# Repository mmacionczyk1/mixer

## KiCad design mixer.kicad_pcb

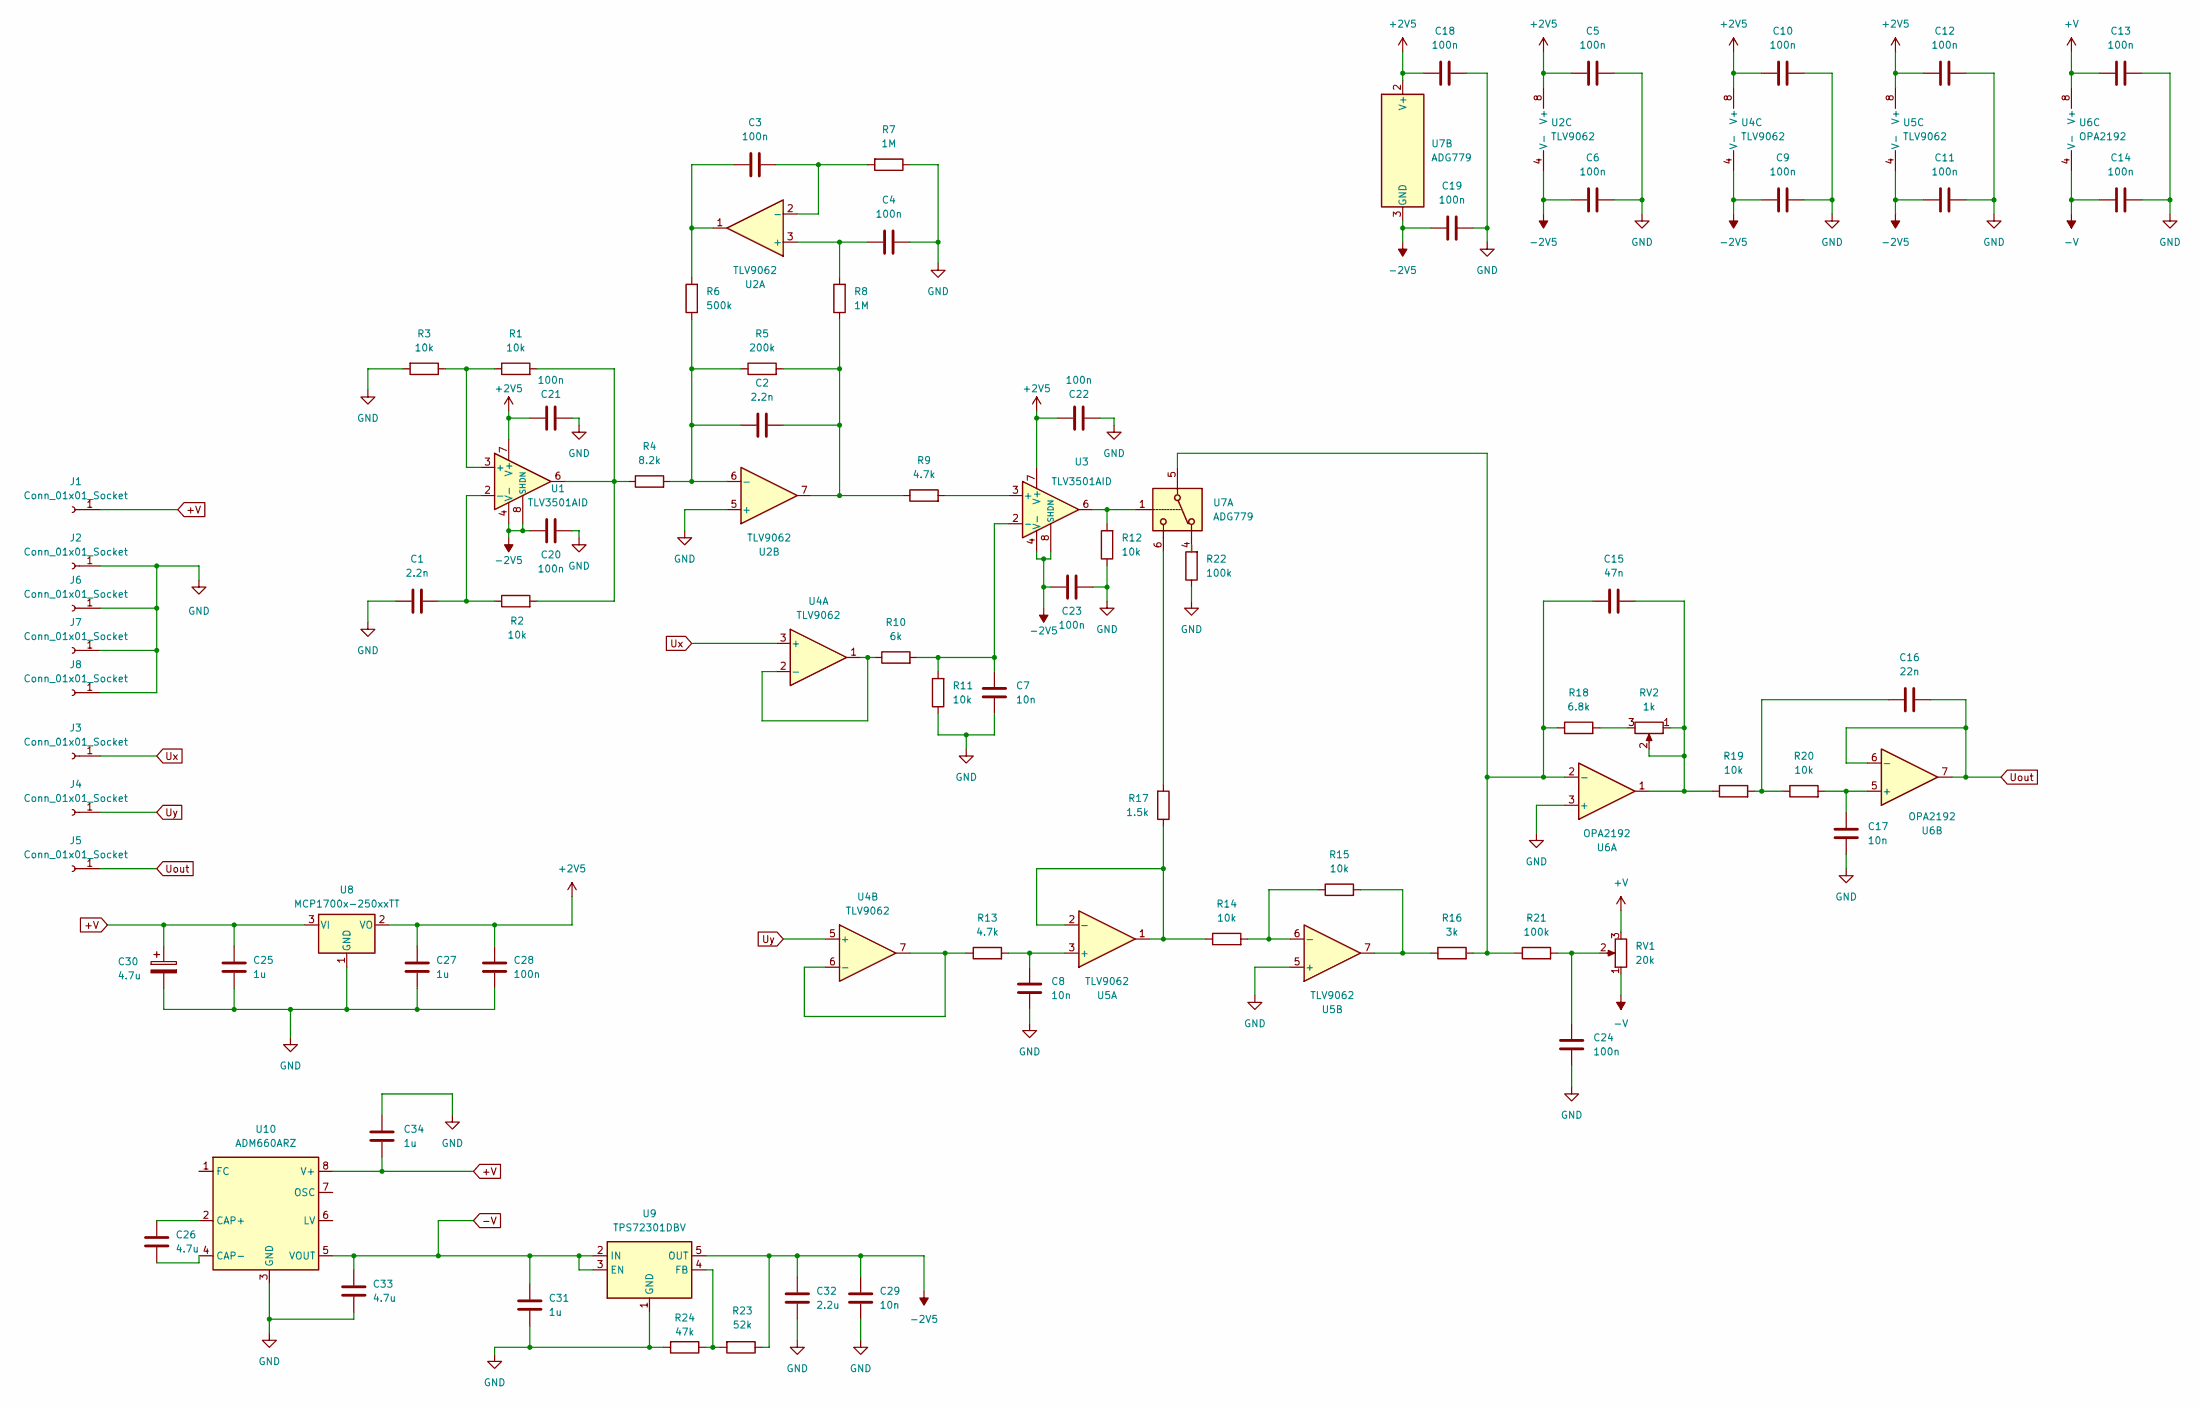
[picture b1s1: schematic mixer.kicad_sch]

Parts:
C1, C2: 2.2n; C_0603_1608Metric_Pad1.08x0.95mm_HandSolder
C3, C4, C5, C6, C9, C10, C11, C12, C13, C14, C18, C19, C20, C21, C22, C23, C24, C28: 100n; C_0603_1608Metric_Pad1.08x0.95mm_HandSolder
C7, C8, C17, C29: 10n; C_0603_1608Metric_Pad1.08x0.95mm_HandSolder
C15: 47n; C_0603_1608Metric_Pad1.08x0.95mm_HandSolder
C16: 22n; C_0603_1608Metric_Pad1.08x0.95mm_HandSolder
C25, C27, C31, C34: 1u; C_0603_1608Metric_Pad1.08x0.95mm_HandSolder
C26, C33: 4.7u; C_0603_1608Metric_Pad1.08x0.95mm_HandSolder
C30: 4.7u; CP_EIA-1608-08_AVX-J_HandSolder
C32: 2.2u; C_0603_1608Metric_Pad1.08x0.95mm_HandSolder
J1, J2, J3, J4, J5, J6, J7, J8: Conn_01x01_Socket; SolderWire-0.5sqmm_1x01_D0.9mm_OD2.3mm
R1, R2, R3, R11, R12, R14, R15, R19, R20: 10k; R_0603_1608Metric_Pad0.98x0.95mm_HandSolder
R4: 8.2k; R_0603_1608Metric_Pad0.98x0.95mm_HandSolder
R5: 200k; R_0603_1608Metric_Pad0.98x0.95mm_HandSolder
R6: 500k; R_0603_1608Metric_Pad0.98x0.95mm_HandSolder
R7, R8: 1M; R_0603_1608Metric_Pad0.98x0.95mm_HandSolder
R9, R13: 4.7k; R_0603_1608Metric_Pad0.98x0.95mm_HandSolder
R10: 6k; R_0603_1608Metric_Pad0.98x0.95mm_HandSolder
R16: 3k; R_0603_1608Metric_Pad0.98x0.95mm_HandSolder
R17: 1.5k; R_0603_1608Metric_Pad0.98x0.95mm_HandSolder
R18: 6.8k; R_0603_1608Metric_Pad0.98x0.95mm_HandSolder
R21, R22: 100k; R_0603_1608Metric_Pad0.98x0.95mm_HandSolder
R23: 52k; R_0603_1608Metric_Pad0.98x0.95mm_HandSolder
R24: 47k; R_0603_1608Metric_Pad0.98x0.95mm_HandSolder
RV1: 20k; Potentiometer_Bourns_3296W_Vertical
RV2: 1k; Potentiometer_Bourns_3296W_Vertical
U1, U3: TLV3501AID; SOIC-8_3.9x4.9mm_P1.27mm
U2, U4, U5: TLV9062; SOIC-8_3.9x4.9mm_P1.27mm
U6: OPA2192; SOIC-8_3.9x4.9mm_P1.27mm
U7: ADG779; SOT-23-6
U8: MCP1700x-250xxTT; SOT-23
U9: TPS72301DBV; SOT-23-5
U10: ADM660ARZ; SOIC-8_3.9x4.9mm_P1.27mm

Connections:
+2V5: C5.1, C10.1, C12.1, C18.1, C21.2, C22.2, C27.2, C28.2, U1.7 (V+), U2.8 (V+), U3.7 (V+), U4.8 (V+), U5.8 (V+), U7.2 (V+), U8.2 (VO)
+V: C13.1, C25.2, C30.1, C34.2, J1.1, RV1.3, U6.8 (V+), U8.3 (VI), U10.8 (V+)
-2V5: C6.1, C9.1, C11.1, C19.1, C20.1, C23.1, C29.2, C32.2, R23.1, U1.4 (V-), U1.8 (SHDN), U2.4 (V-), U3.4 (V-), U3.8 (SHDN), U4.4 (V-), U5.4 (V-), U7.3 (GND), U9.5 (OUT)
-V: C14.1, C31.2, C33.2, RV1.1, U6.4 (V-), U9.2 (IN), U9.3 (EN), U10.5 (VOUT)
GND: C1.1, C4.2, C5.2, C6.2, C7.1, C8.1, C9.2, C10.2, C11.2, C12.2, C13.2, C14.2, C17.1, C18.2, C19.2, C20.2, C21.1, C22.1, C23.2, C24.1, C25.1, C27.1, C28.1, C29.1, C30.2, C31.1, C32.1, C33.1, C34.1, J2.1, J6.1, J7.1, J8.1, R3.2, R7.1, R11.1, R12.1, R22.1, R24.2, U2.5 (+), U5.5 (+), U6.3 (+), U8.1 (GND), U9.1 (GND), U10.3 (GND)
unnamed: C2.2, R5.2, R8.1, R9.1, U2.7
unnamed: C3.1, R6.2, U2.1
unnamed: C15.1, R19.1, RV2.1, RV2.2, U6.1
unnamed: C16.2, R19.2, R20.1
unnamed: C24.2, R21.2, RV1.2
unnamed: R1.2, R2.2, R4.1, U1.6
unnamed: R12.2, U3.6, U7.1
unnamed: R15.2, R16.1, U5.7
unnamed: R17.2, U7.6
unnamed: R18.2, RV2.3
unnamed: R22.2, U7.4
unnamed: R1.1, R3.1, U1.3 (+)
unnamed: C1.2, R2.1, U1.2 (-)
unnamed: C4.1, R8.2, U2.3 (+)
unnamed: C3.2, R7.2, U2.2 (-)
unnamed: C2.1, R4.2, R5.1, R6.1, U2.6 (-)
unnamed: R9.2, U3.3 (+)
unnamed: C7.2, R10.2, R11.2, U3.2 (-)
unnamed: R10.1, U4.1, U4.2 (-)
unnamed: R13.1, U4.6 (-), U4.7
unnamed: C8.2, R13.2, U5.3 (+)
unnamed: R14.1, R17.1, U5.1, U5.2 (-)
unnamed: R14.2, R15.1, U5.6 (-)
unnamed: C15.2, R16.2, R18.1, R21.1, U6.2 (-), U7.5
unnamed: C17.2, R20.2, U6.5 (+)
unnamed: R23.2, R24.1, U9.4 (FB)
unnamed: C26.2, U10.2 (CAP+)
unnamed: C26.1, U10.4 (CAP-)
Uout: C16.1, J5.1, U6.6 (-), U6.7
Ux: J3.1, U4.3 (+)
Uy: J4.1, U4.5 (+)

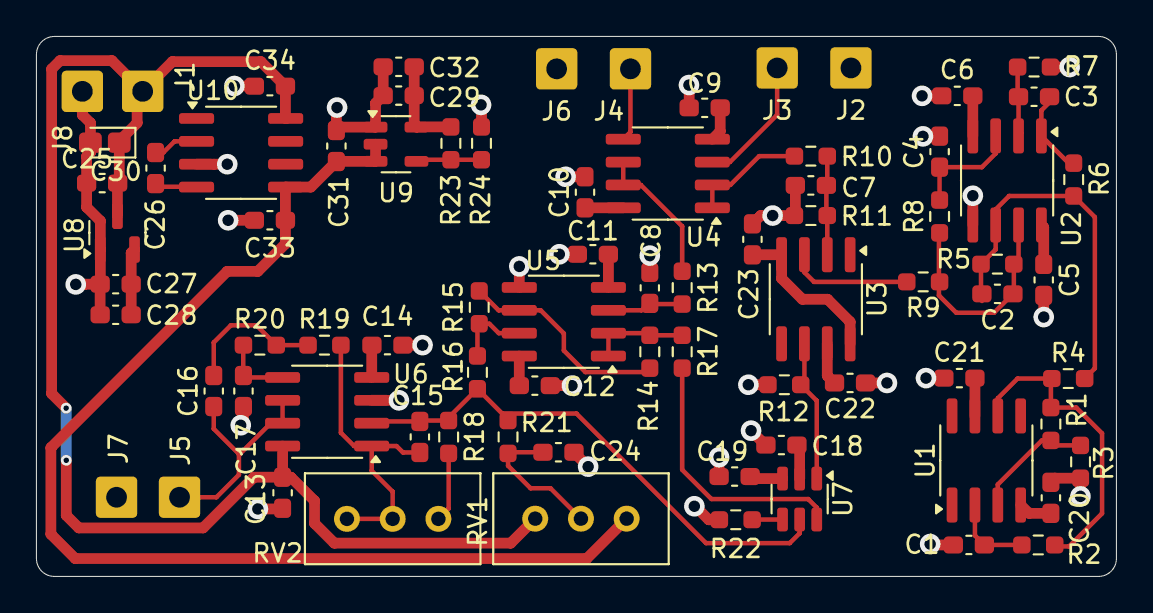
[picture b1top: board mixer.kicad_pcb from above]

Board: 2 copper layers, 60.0 x 30.0 mm, 78 parts (0 on the bottom side), 36 nets.
